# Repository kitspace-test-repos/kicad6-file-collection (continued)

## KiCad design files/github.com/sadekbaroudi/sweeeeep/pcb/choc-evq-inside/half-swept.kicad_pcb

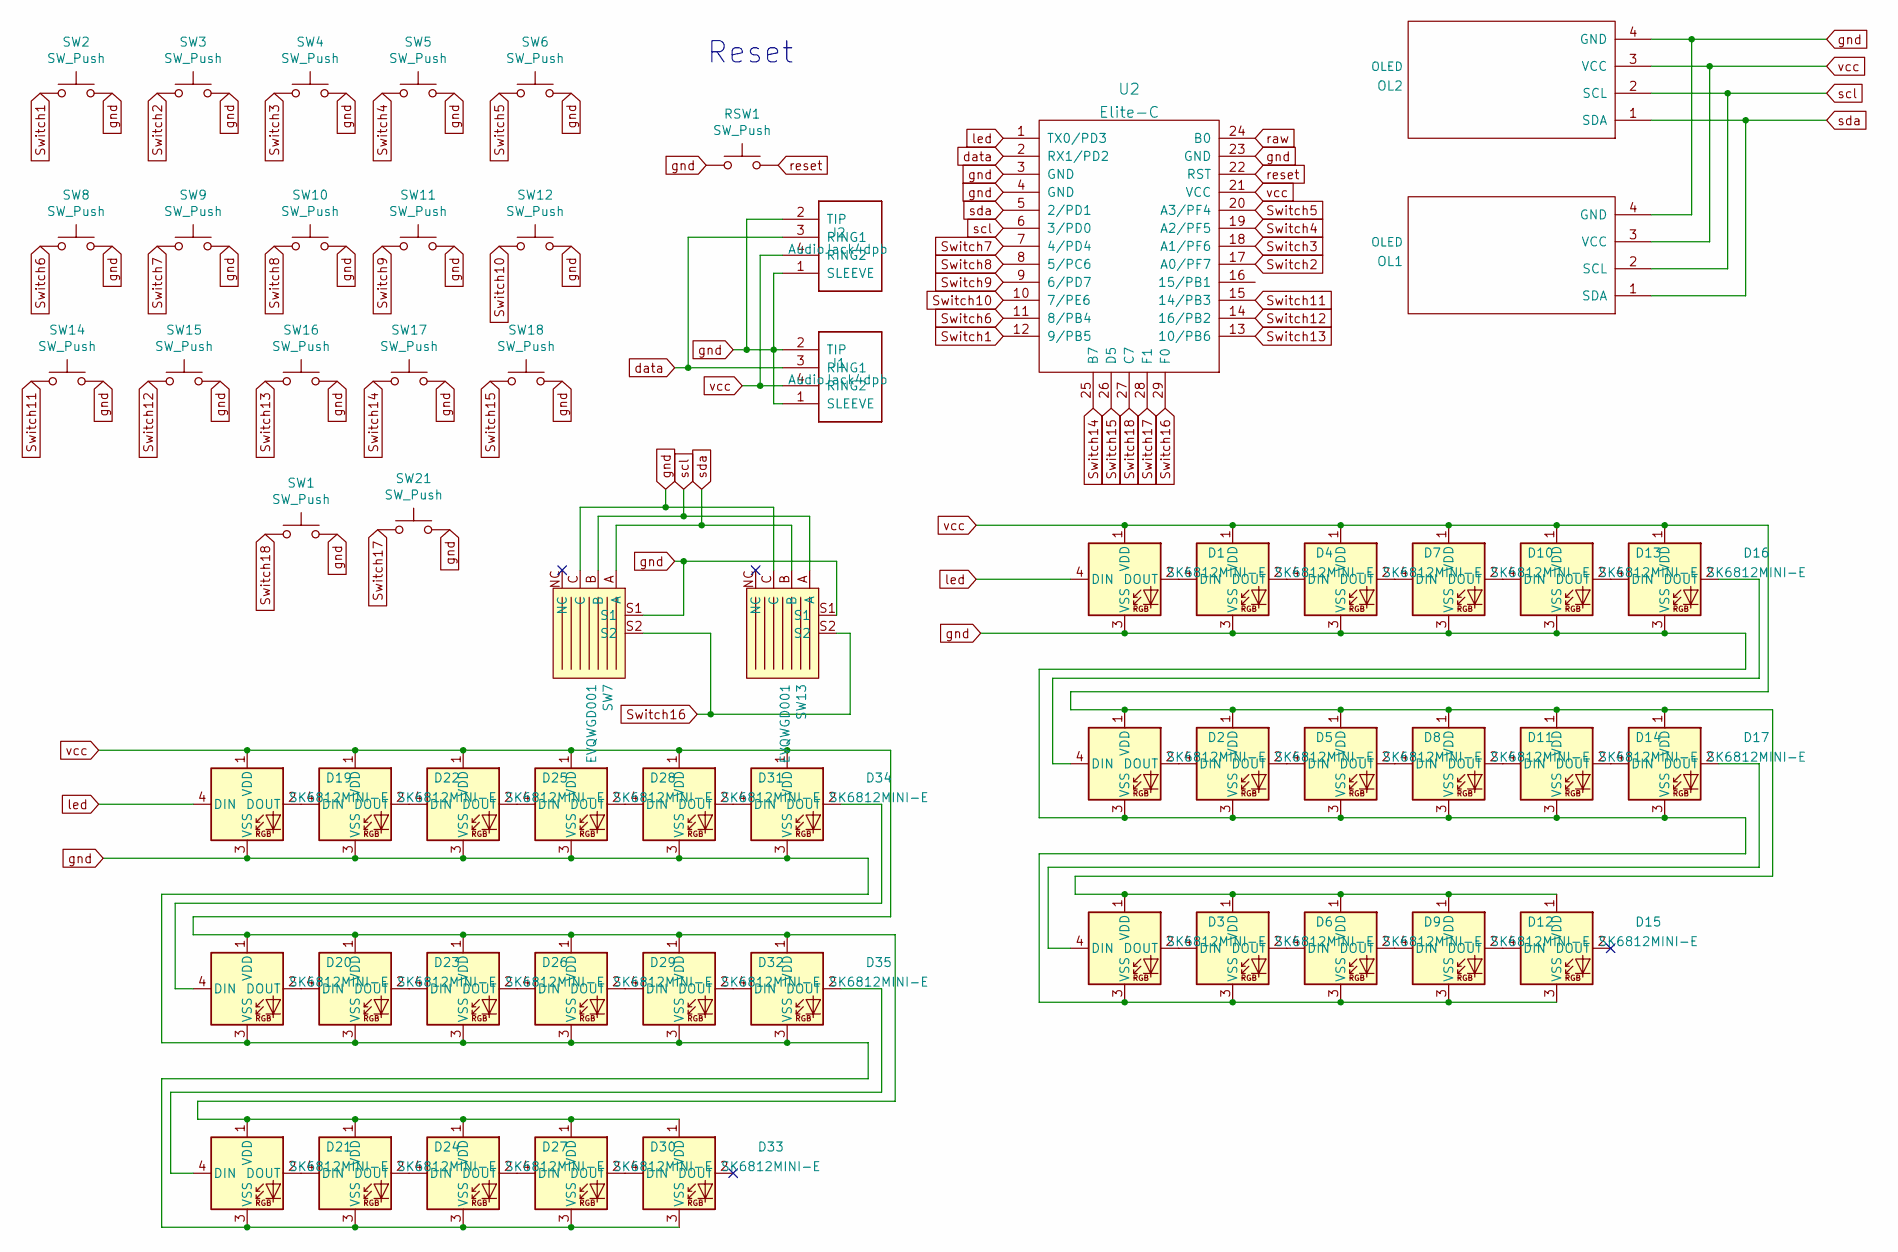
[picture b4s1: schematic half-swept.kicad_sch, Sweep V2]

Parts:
D1, D2, D3, D4, D5, D6, D7, D8, D9, D10, D11, D12, D13, D14, D15, D16, D17, D19, D20, D21, D22, D23, D24, D25, D26, D27, D28, D29, D30, D31, D32, D33, D34, D35: SK6812MINI-E; MX_SK6812MINI-E_REV
J1, J2: AudioJack4dpb; TRRS-PJ-320A
OL1, OL2: OLED; OLED_v2
RSW1: SW_Push; SW_Tactile_SPST_Angled_MJTP1117-no-mount
SW1, SW2, SW3, SW4, SW5, SW6, SW8, SW9, SW10, SW11, SW12, SW14, SW15, SW16, SW17, SW18, SW21: SW_Push; Kailh-PG1350-1u-reversible
SW7, SW13: EVQWGD001; EVQWGD001-no-cutout
U2: Elite-C

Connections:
unnamed: D1.2 (DOUT), D4.4 (DIN)
unnamed: D2.2 (DOUT), D5.4 (DIN)
unnamed: D3.2 (DOUT), D6.4 (DIN)
unnamed: D4.2 (DOUT), D7.4 (DIN)
unnamed: D5.2 (DOUT), D8.4 (DIN)
unnamed: D6.2 (DOUT), D9.4 (DIN)
unnamed: D10.2 (DOUT), D13.4 (DIN)
unnamed: D7.2 (DOUT), D10.4 (DIN)
unnamed: D11.2 (DOUT), D14.4 (DIN)
unnamed: D8.2 (DOUT), D11.4 (DIN)
unnamed: D12.2 (DOUT), D15.4 (DIN)
unnamed: D9.2 (DOUT), D12.4 (DIN)
unnamed: D13.2 (DOUT), D16.4 (DIN)
unnamed: D14.2 (DOUT), D17.4 (DIN)
unnamed: D2.4 (DIN), D16.2 (DOUT)
unnamed: D3.4 (DIN), D17.2 (DOUT)
unnamed: D19.2 (DOUT), D22.4 (DIN)
unnamed: D20.2 (DOUT), D23.4 (DIN)
unnamed: D20.4 (DIN), D34.2 (DOUT)
unnamed: D21.2 (DOUT), D24.4 (DIN)
unnamed: D21.4 (DIN), D35.2 (DOUT)
unnamed: D22.2 (DOUT), D25.4 (DIN)
unnamed: D23.2 (DOUT), D26.4 (DIN)
unnamed: D24.2 (DOUT), D27.4 (DIN)
unnamed: D25.2 (DOUT), D28.4 (DIN)
unnamed: D26.2 (DOUT), D29.4 (DIN)
unnamed: D27.2 (DOUT), D30.4 (DIN)
unnamed: D28.2 (DOUT), D31.4 (DIN)
unnamed: D29.2 (DOUT), D32.4 (DIN)
unnamed: D30.2 (DOUT), D33.4 (DIN)
unnamed: D31.2 (DOUT), D34.4 (DIN)
unnamed: D32.2 (DOUT), D35.4 (DIN)
Switch1: SW2.1, U2.12 (9/PB5)
Switch2: SW3.1, U2.17 (A0/PF7)
Switch3: SW4.1, U2.18 (A1/PF6)
Switch4: SW5.1, U2.19 (A2/PF5)
Switch5: SW6.1, U2.20 (A3/PF4)
Switch6: SW8.1, U2.11 (8/PB4)
Switch7: SW9.1, U2.7 (4/PD4)
Switch8: SW10.1, U2.8 (5/PC6)
Switch9: SW11.1, U2.9 (6/PD7)
Switch10: SW12.1, U2.10 (7/PE6)
Switch11: SW14.1, U2.15 (14/PB3)
Switch12: SW15.1, U2.14 (16/PB2)
Switch13: SW16.1, U2.13 (10/PB6)
Switch14: SW17.1, U2.25 (B7)
Switch15: SW18.1, U2.26 (D5)
Switch16: SW7.S2, SW13.S2, U2.29 (F0)
Switch17: SW21.1, U2.28 (F1)
Switch18: SW1.1, U2.27 (C7)
data: J1.3 (RING1), J2.3 (RING1), U2.2 (RX1/PD2)
gnd: D1.3 (VSS), D2.3 (VSS), D3.3 (VSS), D4.3 (VSS), D5.3 (VSS), D6.3 (VSS), D7.3 (VSS), D8.3 (VSS), D9.3 (VSS), D10.3 (VSS), D11.3 (VSS), D12.3 (VSS), D13.3 (VSS), D14.3 (VSS), D15.3 (VSS), D16.3 (VSS), D17.3 (VSS), D19.3 (VSS), D20.3 (VSS), D21.3 (VSS), D22.3 (VSS), D23.3 (VSS), D24.3 (VSS), D25.3 (VSS), D26.3 (VSS), D27.3 (VSS), D28.3 (VSS), D29.3 (VSS), D30.3 (VSS), D31.3 (VSS), D32.3 (VSS), D33.3 (VSS), D34.3 (VSS), D35.3 (VSS), J1.1 (SLEEVE), J1.2 (TIP), J2.1 (SLEEVE), J2.2 (TIP), OL1.4 (GND), OL2.4 (GND), RSW1.1, SW1.2, SW2.2, SW3.2, SW4.2, SW5.2, SW6.2, SW7.C, SW7.S1, SW8.2, SW9.2, SW10.2, SW11.2, SW12.2, SW13.C, SW13.S1, SW14.2, SW15.2, SW16.2, SW17.2, SW18.2, SW21.2, U2.3 (GND), U2.4 (GND), U2.23 (GND)
led: D1.4 (DIN), D19.4 (DIN), U2.1 (TX0/PD3)
raw: U2.24 (B0)
reset: RSW1.2, U2.22 (RST)
scl: OL1.2 (SCL), OL2.2 (SCL), SW7.B, SW13.A, U2.6 (3/PD0)
sda: OL1.1 (SDA), OL2.1 (SDA), SW7.A, SW13.B, U2.5 (2/PD1)
vcc: D1.1 (VDD), D2.1 (VDD), D3.1 (VDD), D4.1 (VDD), D5.1 (VDD), D6.1 (VDD), D7.1 (VDD), D8.1 (VDD), D9.1 (VDD), D10.1 (VDD), D11.1 (VDD), D12.1 (VDD), D13.1 (VDD), D14.1 (VDD), D15.1 (VDD), D16.1 (VDD), D17.1 (VDD), D19.1 (VDD), D20.1 (VDD), D21.1 (VDD), D22.1 (VDD), D23.1 (VDD), D24.1 (VDD), D25.1 (VDD), D26.1 (VDD), D27.1 (VDD), D28.1 (VDD), D29.1 (VDD), D30.1 (VDD), D31.1 (VDD), D32.1 (VDD), D33.1 (VDD), D34.1 (VDD), D35.1 (VDD), J1.4 (RING2), J2.4 (RING2), OL1.3 (VCC), OL2.3 (VCC), U2.21 (VCC)

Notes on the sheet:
Reset

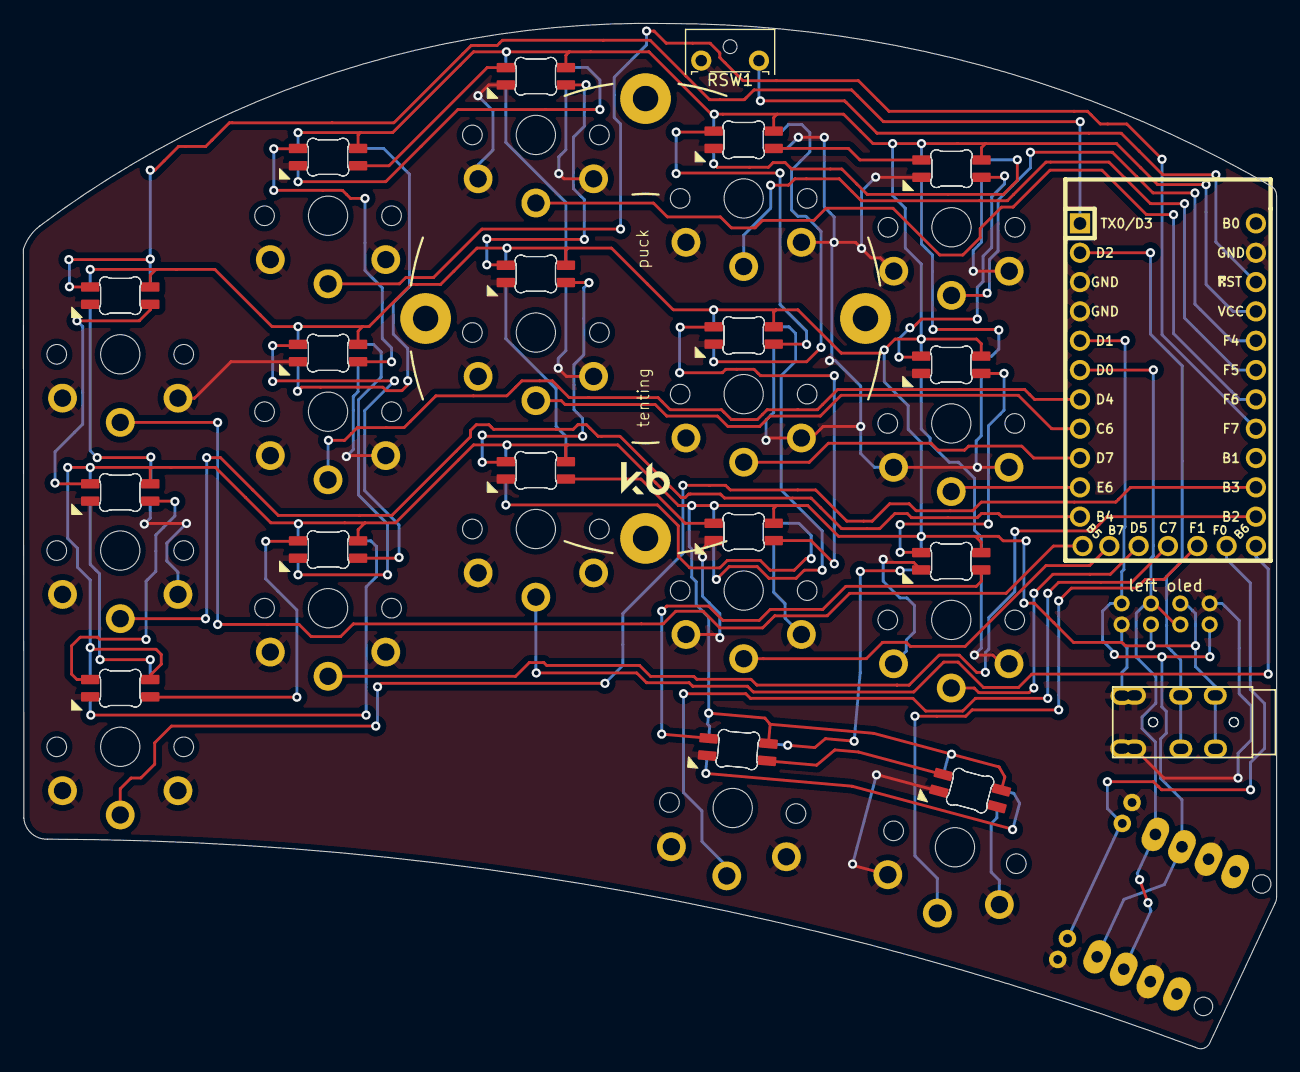
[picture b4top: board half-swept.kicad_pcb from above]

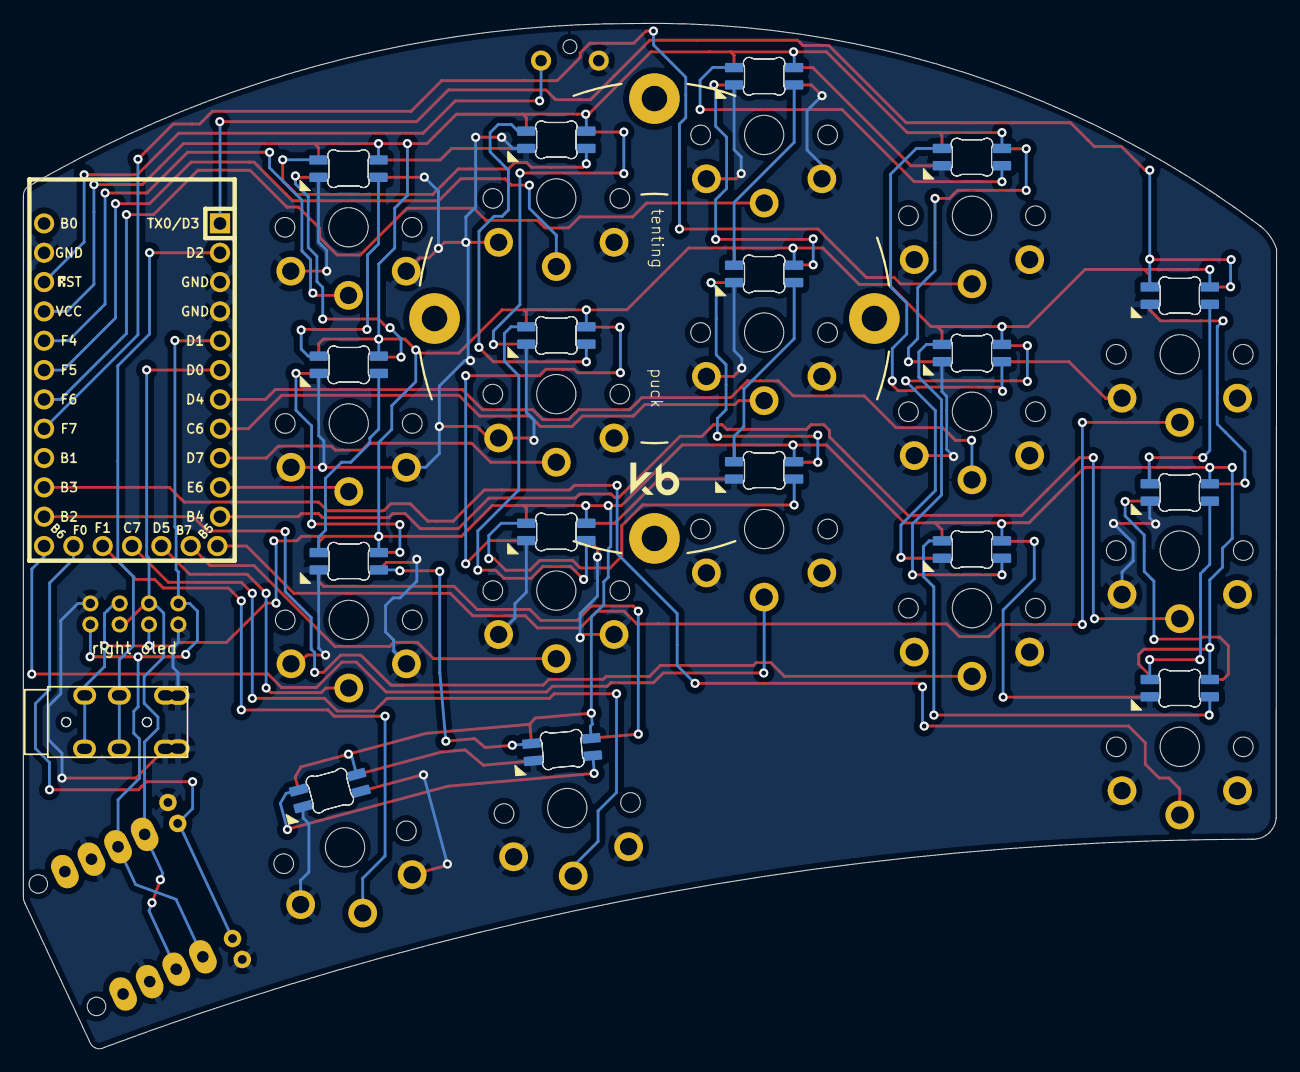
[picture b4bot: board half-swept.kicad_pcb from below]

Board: 2 copper layers, 108.6 x 88.8 mm, 59 parts (20 on the bottom side), 57 nets.

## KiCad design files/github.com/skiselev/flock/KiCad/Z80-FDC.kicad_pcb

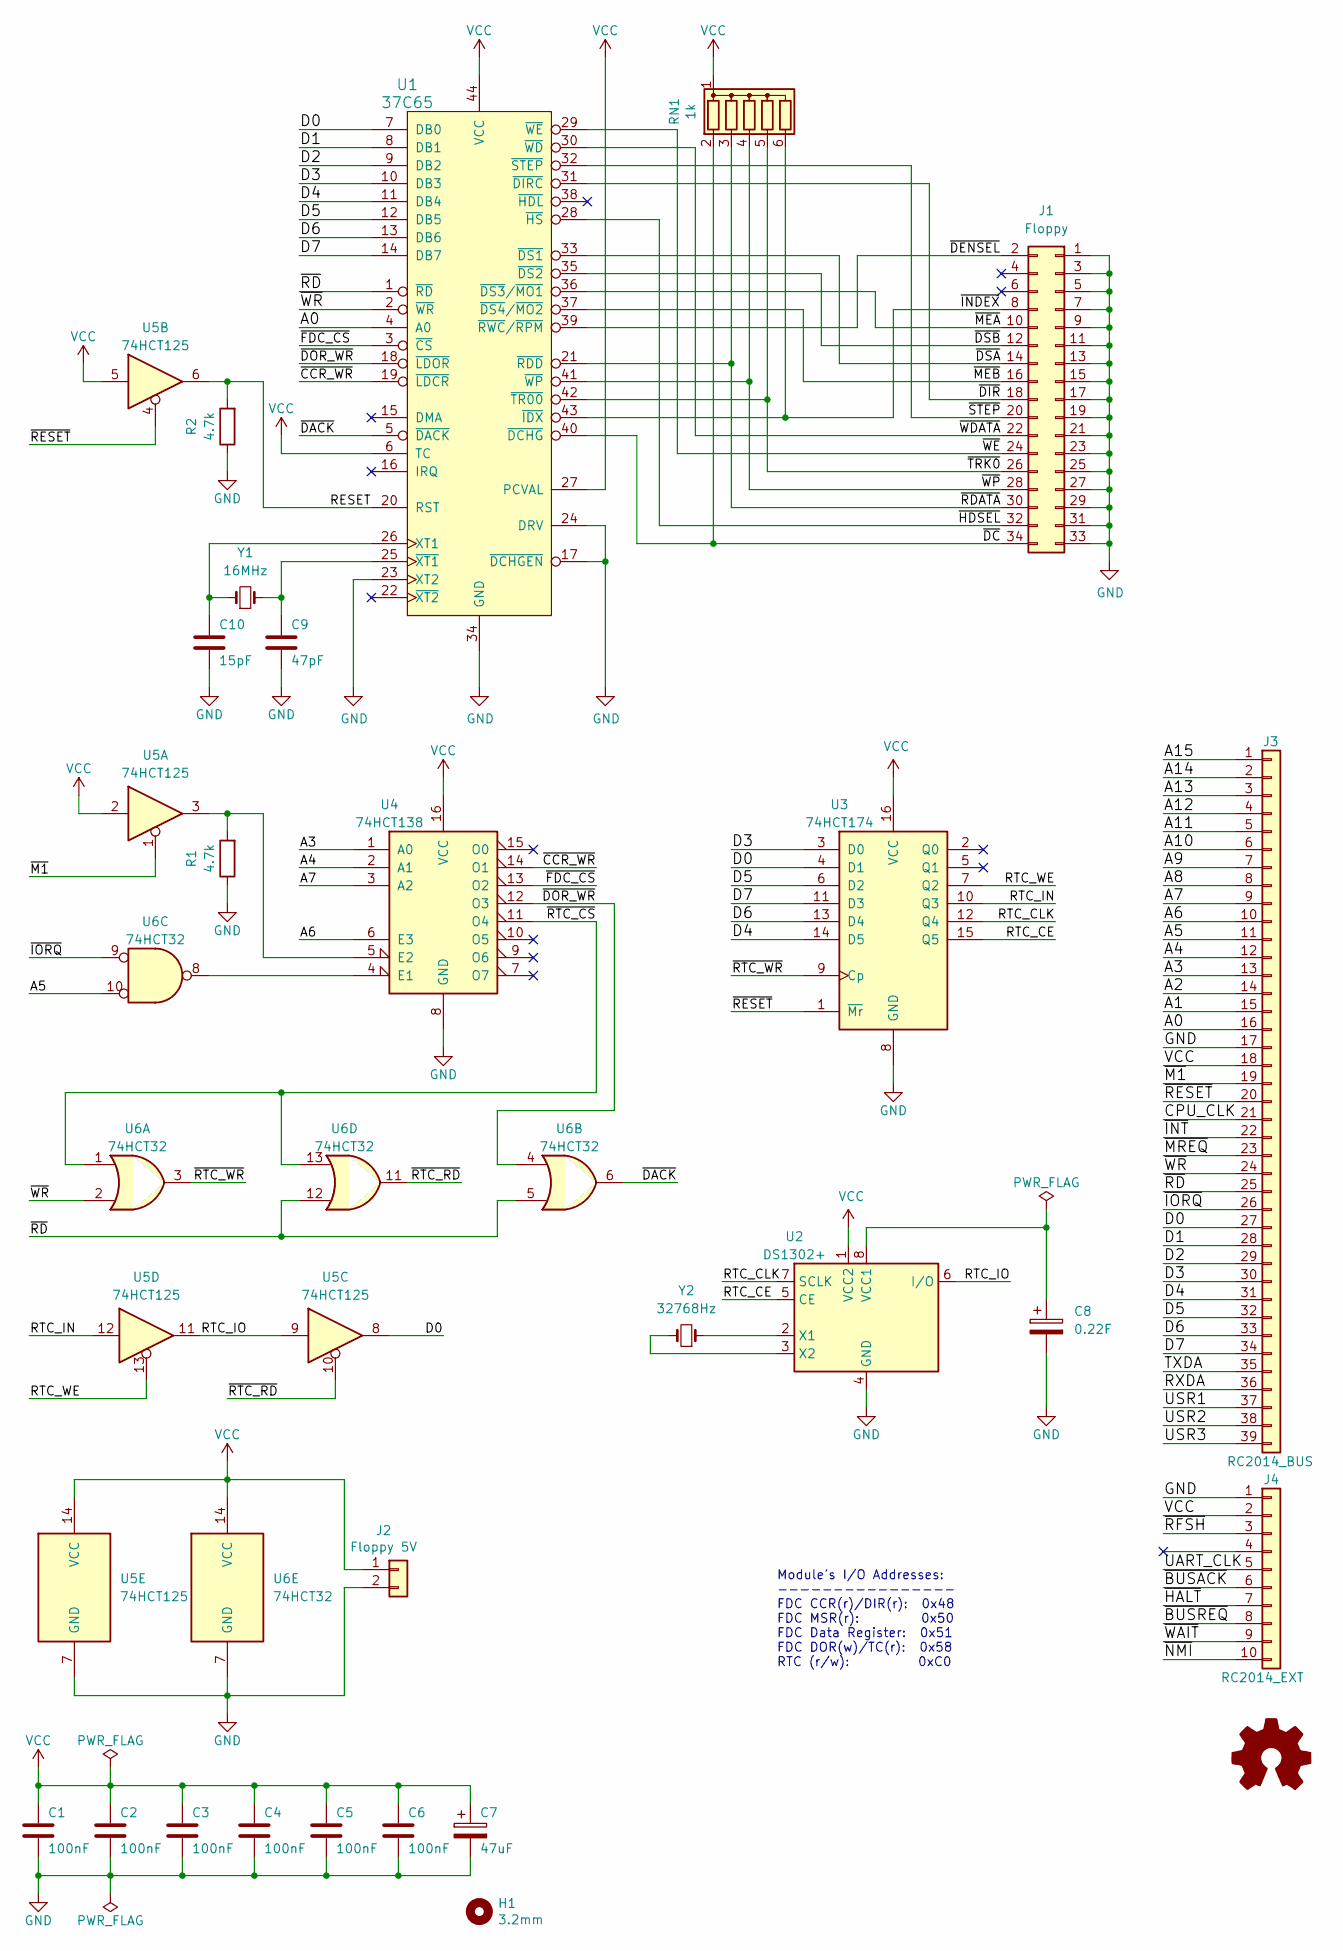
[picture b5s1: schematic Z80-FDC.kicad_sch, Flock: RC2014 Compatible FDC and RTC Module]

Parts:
C1, C2, C3, C4, C5, C6: 100nF; Cap_Cer_508
C7: 47uF; Cap_Elec_Radial_6.3mm
C8: 0.22F; Cap_Super_Radial_13.5mm
C9: 47pF; Cap_Cer_508
C10: 15pF; Cap_Cer_508
H1: 3.2mm; MountingHole_3.2mm_M3_DIN965
J1: Floppy; Conn_Pin_Header_17x2_2.54mm_Shrouded
J2: Floppy 5V; Conn_TE_2-644488-2_2P_2.54mm
J3: RC2014_BUS; Conn_Pin_Header_39x1_2.54mm_Right_Angle
J4: RC2014_EXT; Conn_Pin_Header_10x1_2.54mm_Right_Angle
LOGO1: Logo_Open_Hardware_Small; OSHW-Logo_5.7x6mm_SilkScreen
R1, R2: 4.7k; Res_762
RN1: 1k; Conn_SIL6
U1: 37C65; IC_PLCC44_TH
U2: DS1302+; IC_DIP8_300
U3: 74HCT174; IC_DIP16_300
U4: 74HCT138; IC_DIP16_300
U5: 74HCT125; IC_DIP14_300
U6: 74HCT32; IC_DIP14_300
Y1: 16MHz; Crystal_HC-49U_Vert
Y2: 32768Hz; Crystal_32K_Horiz

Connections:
/A0: J3.16, U1.4 (A0)
/A1: J3.15
/A2: J3.14
/A3: J3.13, U4.1 (A0)
/A4: J3.12, U4.2 (A1)
/A5: J3.11, U6.10
/A6: J3.10, U4.6 (E3)
/A7: J3.9, U4.3 (A2)
/A8: J3.8
/A9: J3.7
/A10: J3.6
/A11: J3.5
/A12: J3.4
/A13: J3.3
/A14: J3.2
/A15: J3.1
/CPU_CLK: J3.21
/D0: J3.27, U1.7 (DB0), U3.4 (D1), U5.8
/D1: J3.28, U1.8 (DB1)
/D2: J3.29, U1.9 (DB2)
/D3: J3.30, U1.10 (DB3), U3.3 (D0)
/D4: J3.31, U1.11 (DB4), U3.14 (D5)
/D5: J3.32, U1.12 (DB5), U3.6 (D2)
/D6: J3.33, U1.13 (DB6), U3.13 (D4)
/D7: J3.34, U1.14 (DB7), U3.11 (D3)
/RESET: R2.2, U1.20 (RST), U5.6
/RTC_CE: U2.5 (CE), U3.15 (Q5)
/RTC_CLK: U2.7 (SCLK), U3.12 (Q4)
/RTC_IN: U3.10 (Q3), U5.12
/RTC_IO: U2.6 (I/O), U5.9, U5.11
/RTC_WE: U3.7 (Q2), U5.13
/RXDA: J3.36
/TXDA: J3.35
/UART_CLK: J4.5
/USR1: J3.37
/USR2: J3.38
/USR3: J3.39
/~BUSACK: J4.6
/~BUSREQ: J4.8
/~CCR_WR: U1.19 (~LDCR), U4.14 (O1)
/~DACK: U1.5 (~DACK), U6.6
/~DC: J1.34, RN1.2 (R1), U1.40 (~DCHG)
/~DENSEL: J1.2, U1.39 (~RWC/~RPM)
/~DIR: J1.18, U1.31 (~DIRC)
/~DOR_WR: U1.18 (~LDOR), U4.12 (O3), U6.4
/~DSA: J1.14, U1.33 (~DS1)
/~DSB: J1.12, U1.35 (~DS2)
/~FDC_CS: U1.3 (~CS), U4.13 (O2)
/~HALT: J4.7
/~HDSEL: J1.32, U1.28 (~HS)
/~INDEX: J1.8, RN1.6 (R5), U1.43 (~IDX)
/~INT: J3.22
/~IORQ: J3.26, U6.9
/~M1: J3.19, U5.1
/~MEA: J1.10, U1.36 (~DS3/~MO1)
/~MEB: J1.16, U1.37 (~DS4/~MO2)
/~MREQ: J3.23
/~NMI: J4.10
/~RDATA: J1.30, RN1.3 (R2), U1.21 (~RDD)
/~RD: J3.25, U1.1 (~RD), U6.5, U6.12
/~RESET: J3.20, U3.1 (~Mr), U5.4
/~RFSH: J4.3
/~RTC_CS: U4.11 (O4), U6.1, U6.13
/~RTC_RD: U5.10, U6.11
/~RTC_WR: U3.9 (Cp), U6.3
/~STEP: J1.20, U1.32 (~STEP)
/~TRK0: J1.26, RN1.5 (R4), U1.42 (~TR00)
/~WAIT: J4.9
/~WDATA: J1.22, U1.30 (~WD)
/~WE: J1.24, U1.29 (~WE)
/~WP: J1.28, RN1.4 (R3), U1.41 (~WP)
/~WR: J3.24, U1.2 (~WR), U6.2
GND: C1.2, C2.2, C3.1, C4.2, C5.2, C6.2, C7.2, C8.2, C9.2, C10.2, J1.1, J1.3, J1.5, J1.7, J1.9, J1.11, J1.13, J1.15, J1.17, J1.19, J1.21, J1.23, J1.25, J1.27, J1.29, J1.31, J1.33, J2.2, J3.17, J4.1, R1.1, R2.1, U1.17 (~DCHGEN), U1.23 (XT2), U1.24 (DRV), U1.34 (GND), U2.4 (GND), U3.8 (GND), U4.8 (GND), U5.7 (GND), U6.7 (GND)
unnamed: C8.1, U2.8 (VCC1)
unnamed: C9.1, U1.25 (~XT1), Y1.2
unnamed: C10.1, U1.26 (XT1), Y1.1
unnamed: R1.2, U4.5 (E2), U5.3
unnamed: U2.2 (X1), Y2.1
unnamed: U2.3 (X2), Y2.2
unnamed: U4.4 (E1), U6.8
VCC: C1.1, C2.1, C3.2, C4.1, C5.1, C6.1, C7.1, J2.1, J3.18, J4.2, RN1.1 (common), U1.6 (TC), U1.27 (PCVAL), U1.44 (VCC), U2.1 (VCC2), U3.16 (VCC), U4.16 (VCC), U5.2, U5.5, U5.14 (VCC), U6.14 (VCC)

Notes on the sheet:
Module's I/O Addresses: ---------------- FDC CCR(r)/DIR(r): 0x48 FDC MSR(r): 0x50 FDC Data Register: 0x51 FDC DOR(w)/TC(r): 0x58 RTC (r/w): 0xC0

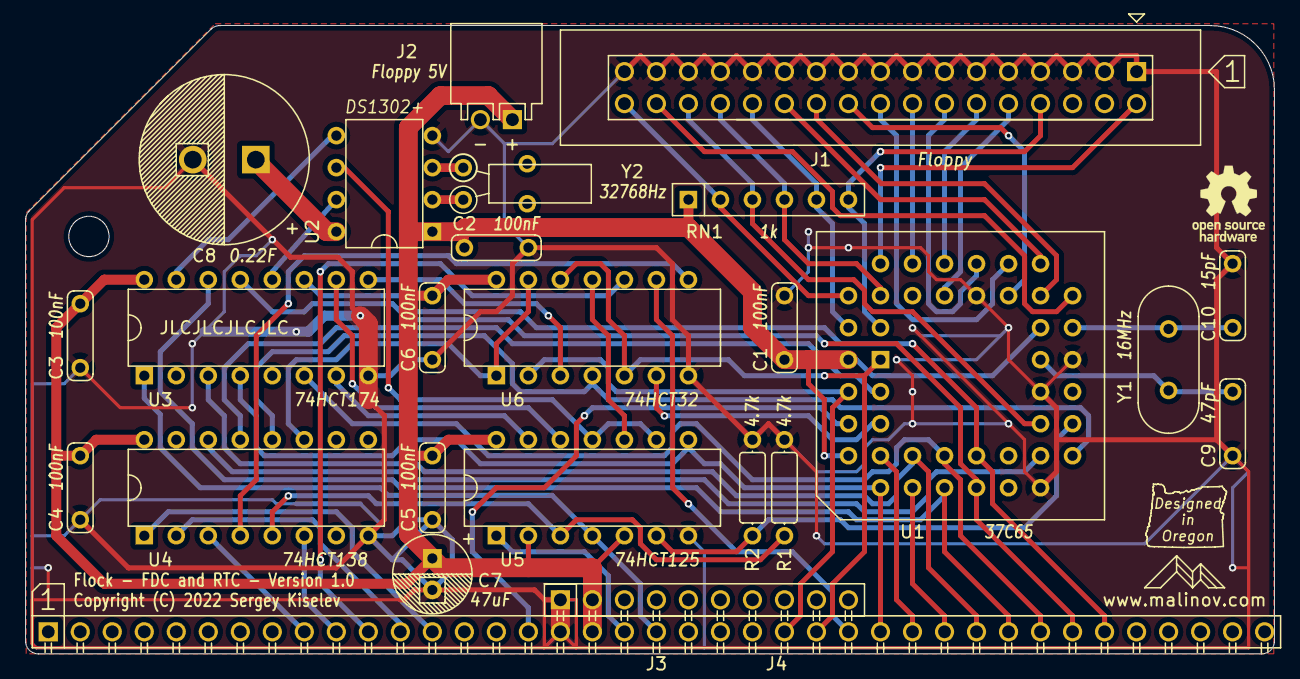
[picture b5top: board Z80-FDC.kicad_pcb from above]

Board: 2 copper layers, 99.1 x 49.9 mm, 28 parts (1 on the bottom side), 56 nets.

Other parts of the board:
LOGO1#2: Logo_Open_Hardware_Small; OSHW-Logo_5.7x6mm_SilkScreen
